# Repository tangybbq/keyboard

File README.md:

# David Brown (d3zd3z) keyboard designs

This repo captures the design files associated with my custom
keyboards.

These keyboards are primarily focused on Steno input, mainly using
[Plover](https://www.openstenoproject.org/plover/). In the spirit of
open steno, I have made these designs open. Anyone is free to make
designs based on these keyboards, for non-commercial purposes.  I am
releasing the designs under the [CC BY-NC
3.0](https://creativecommons.org/licenses/by-nc/3.0/) license.
Specifically, this means if you wish to sell a product based on the
design, you should talk to me.

## The "Jolt" keyboard

At this point, I've decided to give the keyboard a real name, hence "jolt".  The jolt 1 is still in
Eagle, and I may migrate the files here.

But, I have added the "jolt2".  The jolt2 is an experiment beyond just a traditional corne-like
keyboard, and something fully in 3-space, like the dactyl.  There are individual base plates for
left and right, and then small strips of 3 keys for each column.  The base PCB has 4 pairs of pin
headers to support these individual 3-key columns.  This will allow me to experiment with elevation
as well as just the X and Y position of each key.  I still want each column to be at the same
elevation, because I rely heavily on pressing keys together (both for my qwerty layout, and for
steno).

At this point, there are 4 PCBs here:

- [jolt2-left](jolt2/jolt2-left/): The layout of the left
  side using a directly assembled rp2040
- [jolt2-tiny2040-left](jolt2/jolt2-tiny2040-left/): The same left side pcb, but built around the [Pimoroni
  Tiny 2040](https://shop.pimoroni.com/products/tiny-2040?variant=39560012234835).  Note that only
  the left side needs the 8MB version (to hold the steno dictionary), but I just ordered all the
  same, and use the 8MB version on each side.
- [jolt2-tiny2040-right](jolt2/jolt2-tiny2040-right/): The Tiny 2040-based, made for the right side.
- [jolt2-verts](jolt2/jolt2-verts/): These are the small 3-key support boards.  It will take 28 of these,
  plus a left and a right to build a full keyboard.

In addition, there is also a [jolt2-pim-left](jolt2/jolt2-pim-left/), based around the [Pimoroni
PGA2350](https://shop.pimoroni.com/products/pga2350?variant=42092629229651).  There are numerous
errors in this that need to be fixed, as I messed up the reference numbers for the headers to the
key-boards.

## The "bletest2"

This isn't really a keyboard, but my experiments putting an nRF5340 module on a board.  This is work
in progress, and has numerous things I've discovered wrong with it.  I will work to improve it over
time:

- The power supply was suppose to auto switch between USB power and battery power.  However, I
  accidentally chose a boost converter instead of a boost/buck converter, and if USB is connected,
  all it does is fry everything on the board.  You can either leave out D1, or install a chain of
  diodes in its place (I used 5) to drop the voltage enough to make VBUS less than the 3.3.
  Auto-switching will probably end up preferring the battery, though, so I just recommend removing
  D1 entirely, and powering the board off of the batteries.
- The RGB LEDs don't work.  I'm not quite sure what is wrong, as I see no signal on the DIN pin.  I
  maybe have issues, given the difficult of properly soldering down the BLE module.
- The LEDs probably need a 5V supply, which isn't readily available.  Realistically, if I build a
  battery power device, I'll likely just use an analog RGB component, and use 3 gpios with PWM.

The intent was to be able to remove the various jumpers, and use the Power Profiler Kit II to
observer power consumption.  Despite rev 2, I'm still not far enough along with this to be able to
do that meaningfully.

## The "shield-kb1"

This is an Arduino-style shield, designed to plug into the nRF5340 DK.  It provides non-working
LEDs, a 2x2 keyboard matrix, and inter-board headers for left and right that should allow it to talk
to the jolt or proto3 designs.

## The "proto3"

This is basically the same design as the proto2, but with a third row.
The qmk supports an easier qwerty mode, but still with a modified
homerow modifier support (I use the lower row as it has slightly fewer
rollover conflicts).

The BOM is the same as the proto2, but it will need 42 diodes.

## The "proto2"

For lack of a better name, this first design is called the "proto2".

There was an earlier prototype, that was handwired, and rather
fragile.  This is the first version I would consider to be a usable
keyboard.  In the above pictures, the left half has the MCU (Pro Micro
RP2040) soldered directly to a header, soldered to the PCB, and the
right one uses a socket.

To build this, in addition to the PCBs, you will need

- 2 [Pro Micro RP2040](https://www.sparkfun.com/products/18288)
  boards.  At the time of my build, these are running about $11, and
  seem readily available.
- 30 Kailh Choc switches.  I sourced mine from
  [Mkultra](https://mkultra.click/choc-switches).  I recommend the
  "pink" version, which has 20gf springs, and I find work well.
- 30 keycaps for these switches.  I used the [MBK Factory
  Colors](https://mkultra.click/mbk-factory-colors/) keycaps, which
  allows me to make the "primary" keys stand out a little, and just
  looks rather nice.
- 30 general purpose SOD123 diodes.  I got
  [BAV19W](https://www.digikey.com/en/products/detail/smc-diode-solutions/BAV19W/5993796),
  although almost any diode will work for this.
- 2 or 4 5-pin right angle headers.  Two are needed for the
  communication between the boards.  The others are interested if you
  want to use SWD, since the RP2040 Pro Micro inconveniently puts
  these connectors on the underside of the board.

The PCB is reversable.  The RP2040 board should be mounted in the
labeled holes, which is always the left set when viewed from the top.
The diodes are intended to be soldered to the bottom side of the
board.

I have also a case design that can be 3d printed.  The models are for
the right side. Use your slicing software to mirror about the X axis
to print the pieces for the other side.

The firmware I am using for this keyboard is in my fork of
[QMK](https://github.com/tangybbq/qmk_firmware/tree/proto2).

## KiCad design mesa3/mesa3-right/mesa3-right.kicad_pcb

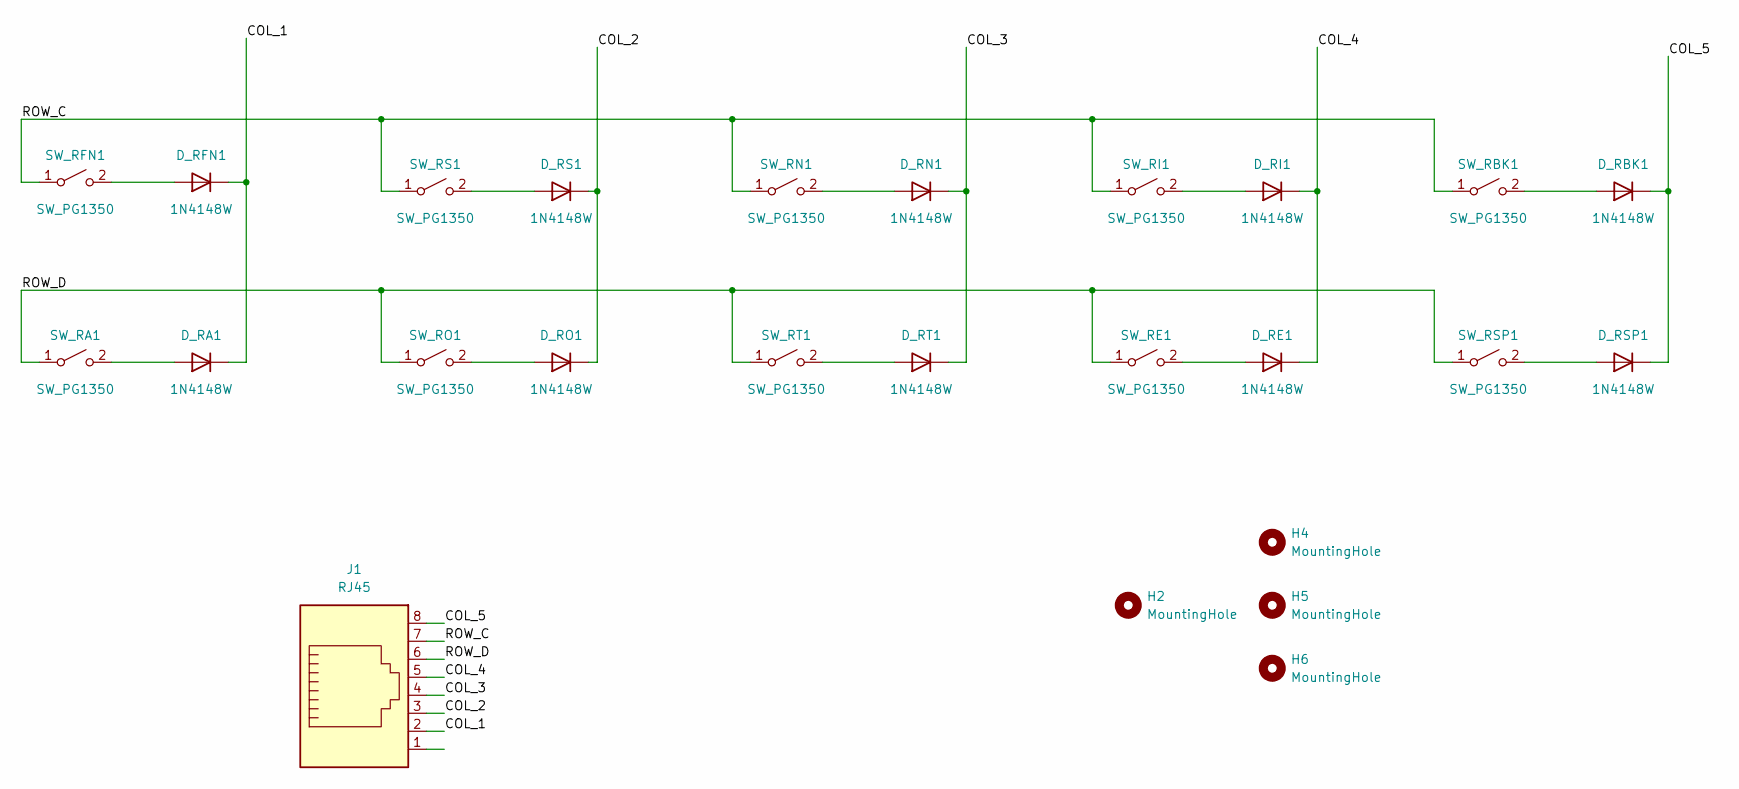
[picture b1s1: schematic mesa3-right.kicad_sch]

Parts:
D_RA1: 1N4148W; D_SOD-123
D_RBK1: 1N4148W; D_SOD-123
D_RE1: 1N4148W; D_SOD-123
D_RFN1: 1N4148W; D_SOD-123
D_RI1: 1N4148W; D_SOD-123
D_RN1: 1N4148W; D_SOD-123
D_RO1: 1N4148W; D_SOD-123
D_RS1: 1N4148W; D_SOD-123
D_RSP1: 1N4148W; D_SOD-123
D_RT1: 1N4148W; D_SOD-123
H2, H4, H5, H6: MountingHole; MountingHole_2.2mm_M2
J1: RJ45; RJ45_Amphenol_54602-x08_Horizontal
SW_RA1: SW_PG1350; Kailh_socket_PG1350
SW_RBK1: SW_PG1350; Kailh_socket_PG1350
SW_RE1: SW_PG1350; Kailh_socket_PG1350
SW_RFN1: SW_PG1350; Kailh_socket_PG1350
SW_RI1: SW_PG1350; Kailh_socket_PG1350
SW_RN1: SW_PG1350; Kailh_socket_PG1350
SW_RO1: SW_PG1350; Kailh_socket_PG1350
SW_RS1: SW_PG1350; Kailh_socket_PG1350
SW_RSP1: SW_PG1350; Kailh_socket_PG1350
SW_RT1: SW_PG1350; Kailh_socket_PG1350

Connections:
/COL_1: D_RA1.1 (K), D_RFN1.1 (K), J1.2
/COL_2: D_RO1.1 (K), D_RS1.1 (K), J1.3
/COL_3: D_RN1.1 (K), D_RT1.1 (K), J1.4
/COL_4: D_RE1.1 (K), D_RI1.1 (K), J1.5
/COL_5: D_RBK1.1 (K), D_RSP1.1 (K), J1.8
/ROW_C: J1.7, SW_RBK1.1 (A), SW_RFN1.1 (A), SW_RI1.1 (A), SW_RN1.1 (A), SW_RS1.1 (A)
/ROW_D: J1.6, SW_RA1.1 (A), SW_RE1.1 (A), SW_RO1.1 (A), SW_RSP1.1 (A), SW_RT1.1 (A)
unnamed: D_RA1.2 (A), SW_RA1.2 (B)
unnamed: D_RBK1.2 (A), SW_RBK1.2 (B)
unnamed: D_RE1.2 (A), SW_RE1.2 (B)
unnamed: D_RFN1.2 (A), SW_RFN1.2 (B)
unnamed: D_RI1.2 (A), SW_RI1.2 (B)
unnamed: D_RN1.2 (A), SW_RN1.2 (B)
unnamed: D_RO1.2 (A), SW_RO1.2 (B)
unnamed: D_RS1.2 (A), SW_RS1.2 (B)
unnamed: D_RSP1.2 (A), SW_RSP1.2 (B)
unnamed: D_RT1.2 (A), SW_RT1.2 (B)

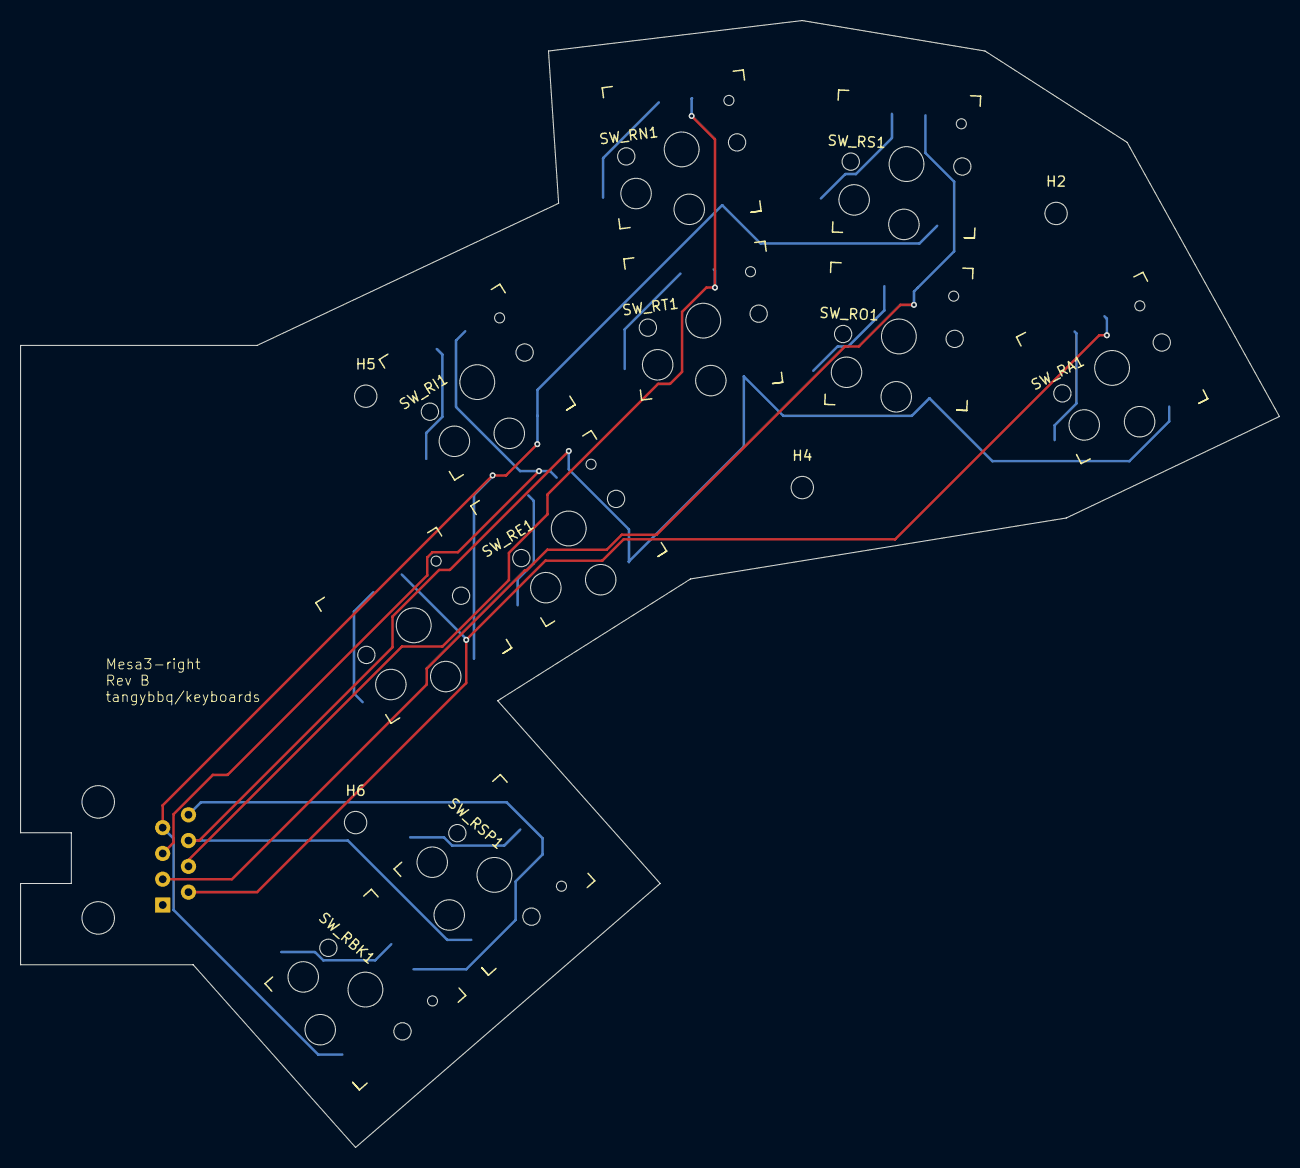
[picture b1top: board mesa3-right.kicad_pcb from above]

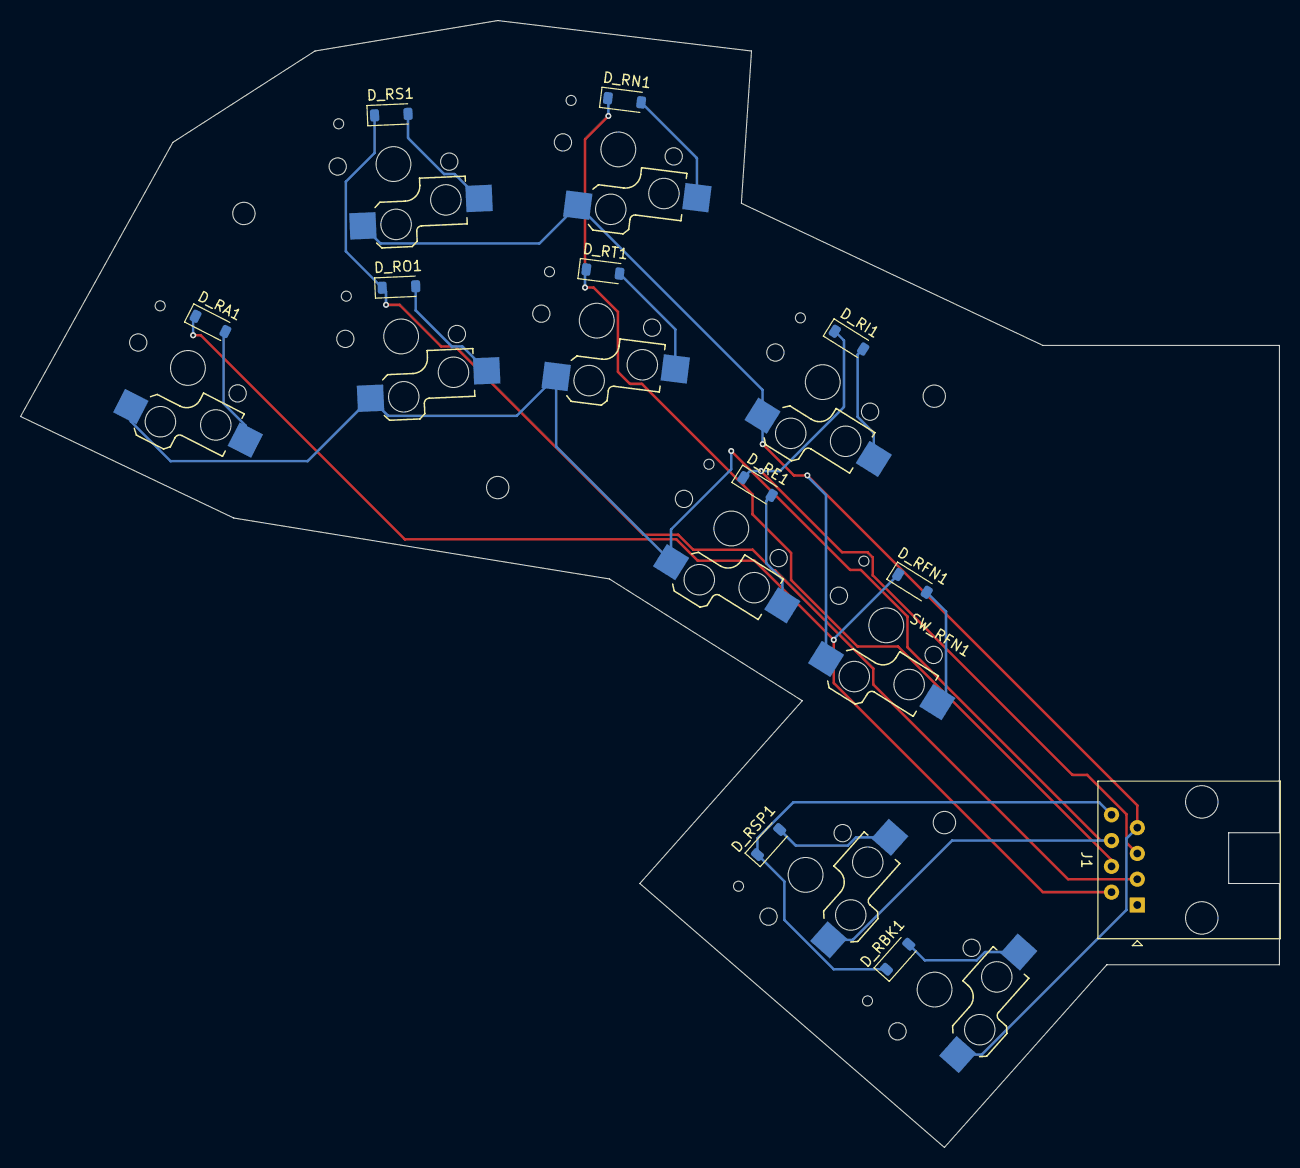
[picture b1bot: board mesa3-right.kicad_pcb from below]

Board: 2 copper layers, 124.0 x 111.0 mm, 25 parts (11 on the bottom side), 17 nets.

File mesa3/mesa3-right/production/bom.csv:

Designator,Footprint,Quantity,Value,LCSC Part #
"D_RA1, D_RBK1, D_RE1, D_RI1, D_RN1, D_RO1, D_RS1, D_RSP1, D_RT1",D_SOD-123,9,1N4148W,
J1,RJ45_Amphenol_54602-x08_Horizontal,1,RJ45,
"SW_RA1, SW_RBK1, SW_RE1, SW_RI1, SW_RN1, SW_RO1, SW_RS1, SW_RSP1, SW_RT1",Kailh_socket_PG1350,9,SW_PG1350,

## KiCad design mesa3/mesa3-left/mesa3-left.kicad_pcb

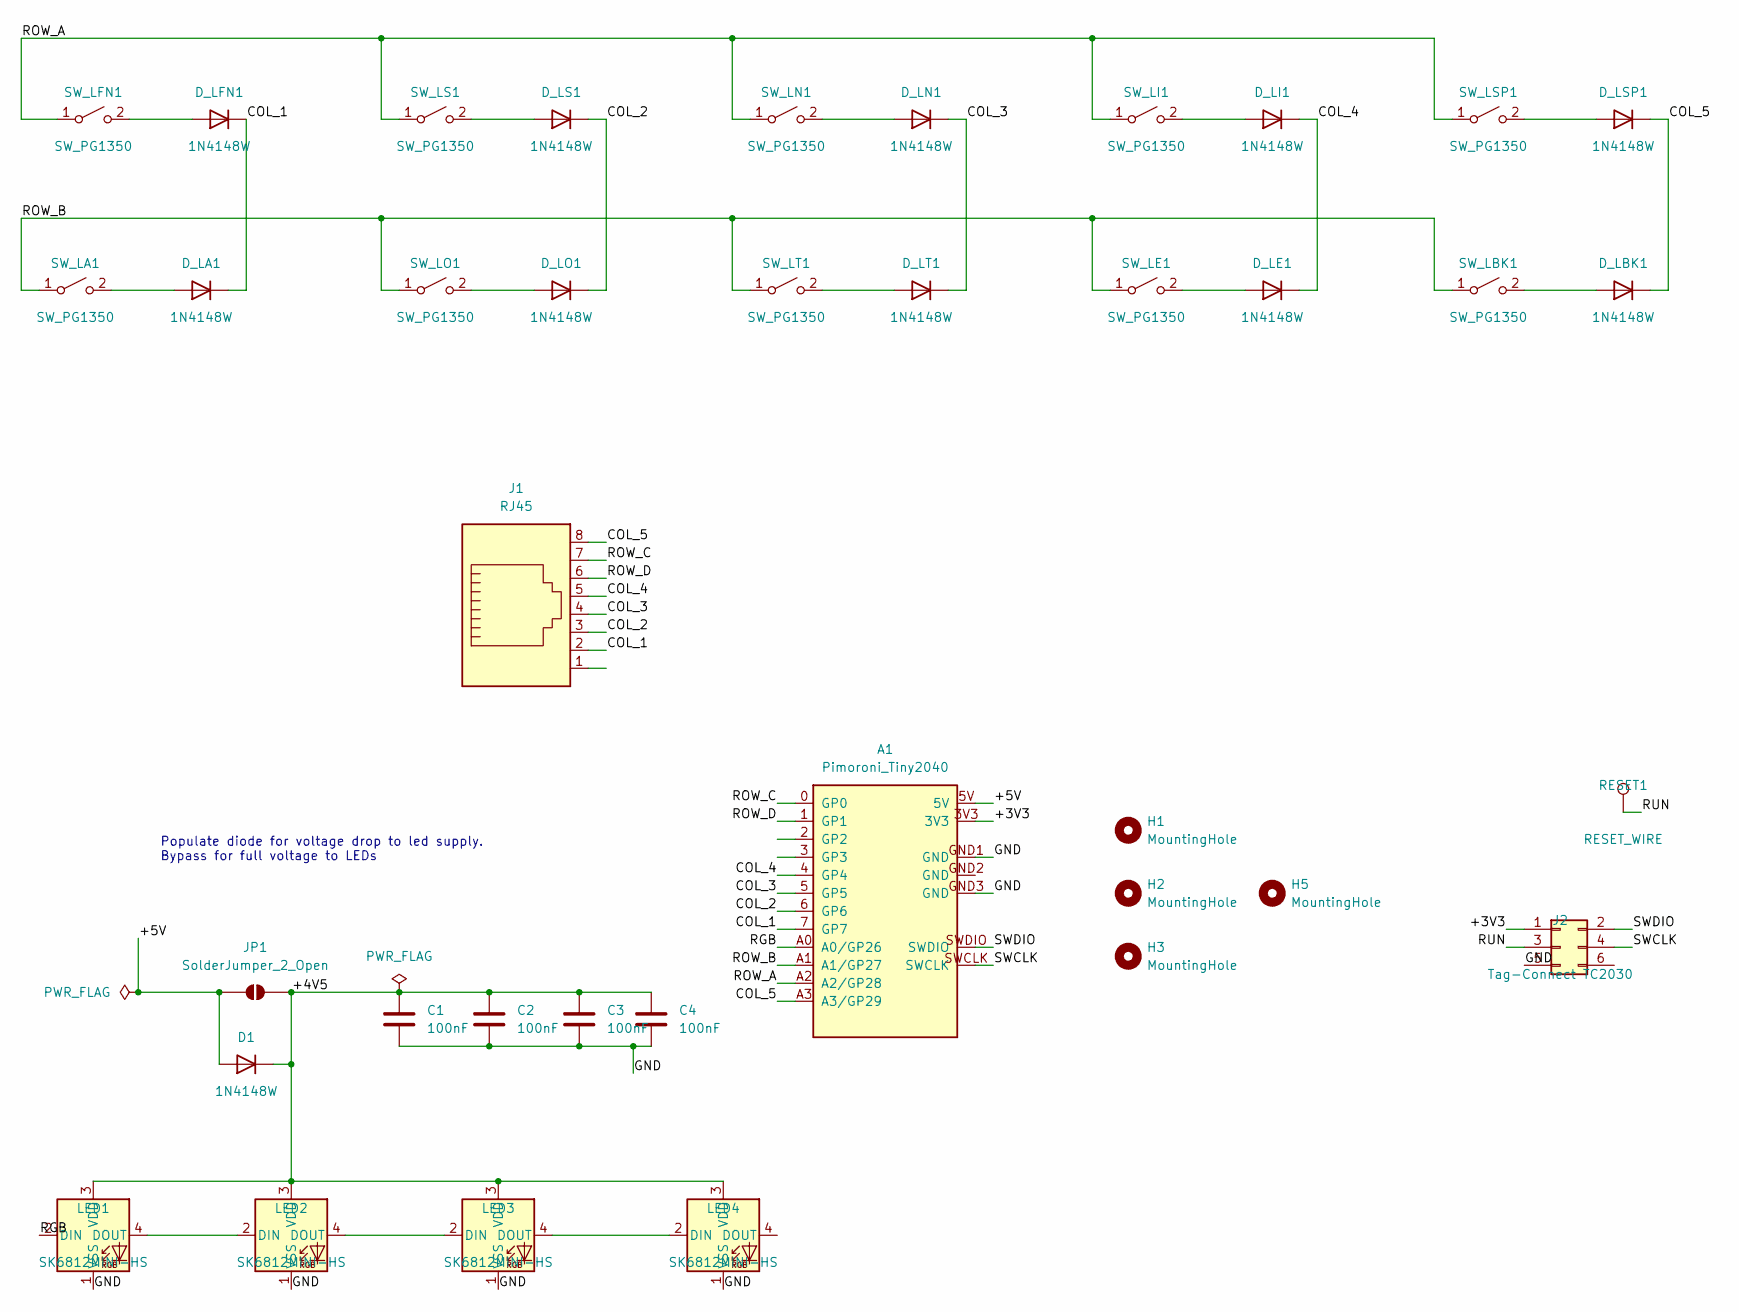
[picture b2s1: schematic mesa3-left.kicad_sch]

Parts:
A1: Pimoroni_Tiny2040
C1, C2, C3, C4: 100nF; C_0603_1608Metric_Pad1.08x0.95mm_HandSolder
D1: 1N4148W; D_SOD-123
D_LA1: 1N4148W; D_SOD-123
D_LBK1: 1N4148W; D_SOD-123
D_LE1: 1N4148W; D_SOD-123
D_LFN1: 1N4148W; D_SOD-123
D_LI1: 1N4148W; D_SOD-123
D_LN1: 1N4148W; D_SOD-123
D_LO1: 1N4148W; D_SOD-123
D_LS1: 1N4148W; D_SOD-123
D_LSP1: 1N4148W; D_SOD-123
D_LT1: 1N4148W; D_SOD-123
H1, H2, H3, H5: MountingHole; MountingHole_2.2mm_M2
J1: RJ45; RJ45_Amphenol_54602-x08_Horizontal
J2: Tag-Connect TC2030; Tag-Connect_TC2030-IDC-FP_2x03_P1.27mm_Vertical
JP1: SolderJumper_2_Open; SolderJumper-2_P1.3mm_Open_RoundedPad1.0x1.5mm
LED1, LED2, LED3, LED4: SK6812MINI-HS; SK6812-MINI-HS
RESET1: RESET_WIRE; TestPoint_Pad_2.0x2.0mm
SW_LA1: SW_PG1350; Kailh_socket_PG1350
SW_LBK1: SW_PG1350; Kailh_socket_PG1350
SW_LE1: SW_PG1350; Kailh_socket_PG1350
SW_LFN1: SW_PG1350; Kailh_socket_PG1350
SW_LI1: SW_PG1350; Kailh_socket_PG1350
SW_LN1: SW_PG1350; Kailh_socket_PG1350
SW_LO1: SW_PG1350; Kailh_socket_PG1350
SW_LS1: SW_PG1350; Kailh_socket_PG1350
SW_LSP1: SW_PG1350; Kailh_socket_PG1350
SW_LT1: SW_PG1350; Kailh_socket_PG1350

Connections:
/+3V3: A1.3V3, J2.1
/+4V5: C1.1, C2.1, C3.1, C4.1, D1.1 (K), JP1.2 (B), LED1.3 (VDD), LED2.3 (VDD), LED3.3 (VDD), LED4.3 (VDD)
/+5V: A1.5V, D1.2 (A), JP1.1 (A)
/COL_1: A1.7 (GP7), D_LA1.1 (K), D_LFN1.1 (K), J1.2
/COL_2: A1.6 (GP6), D_LO1.1 (K), D_LS1.1 (K), J1.3
/COL_3: A1.5 (GP5), D_LN1.1 (K), D_LT1.1 (K), J1.4
/COL_4: A1.4 (GP4), D_LE1.1 (K), D_LI1.1 (K), J1.5
/COL_5: A1.A3 (A3/GP29), D_LBK1.1 (K), D_LSP1.1 (K), J1.8
/GND: A1.GND1 (GND), A1.GND3 (GND), C1.2, C2.2, C3.2, C4.2, J2.5, LED1.1 (VSS), LED2.1 (VSS), LED3.1 (VSS), LED4.1 (VSS)
/RGB: A1.A0 (A0/GP26), LED1.2 (DIN)
/ROW_A: A1.A2 (A2/GP28), SW_LFN1.1 (A), SW_LI1.1 (A), SW_LN1.1 (A), SW_LS1.1 (A), SW_LSP1.1 (A)
/ROW_B: A1.A1 (A1/GP27), SW_LA1.1 (A), SW_LBK1.1 (A), SW_LE1.1 (A), SW_LO1.1 (A), SW_LT1.1 (A)
/ROW_C: A1.0 (GP0), J1.7
/ROW_D: A1.1 (GP1), J1.6
/RUN: J2.3, RESET1.1 (1_1)
/SWCLK: A1.SWCLK, J2.4
/SWDIO: A1.SWDIO, J2.2
unnamed: D_LA1.2 (A), SW_LA1.2 (B)
unnamed: D_LBK1.2 (A), SW_LBK1.2 (B)
unnamed: D_LE1.2 (A), SW_LE1.2 (B)
unnamed: D_LFN1.2 (A), SW_LFN1.2 (B)
unnamed: D_LI1.2 (A), SW_LI1.2 (B)
unnamed: D_LN1.2 (A), SW_LN1.2 (B)
unnamed: D_LO1.2 (A), SW_LO1.2 (B)
unnamed: D_LS1.2 (A), SW_LS1.2 (B)
unnamed: D_LSP1.2 (A), SW_LSP1.2 (B)
unnamed: D_LT1.2 (A), SW_LT1.2 (B)
unnamed: LED1.4 (DOUT), LED2.2 (DIN)
unnamed: LED2.4 (DOUT), LED3.2 (DIN)
unnamed: LED3.4 (DOUT), LED4.2 (DIN)

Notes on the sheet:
Populate diode for voltage drop to led supply. Bypass for full voltage to LEDs

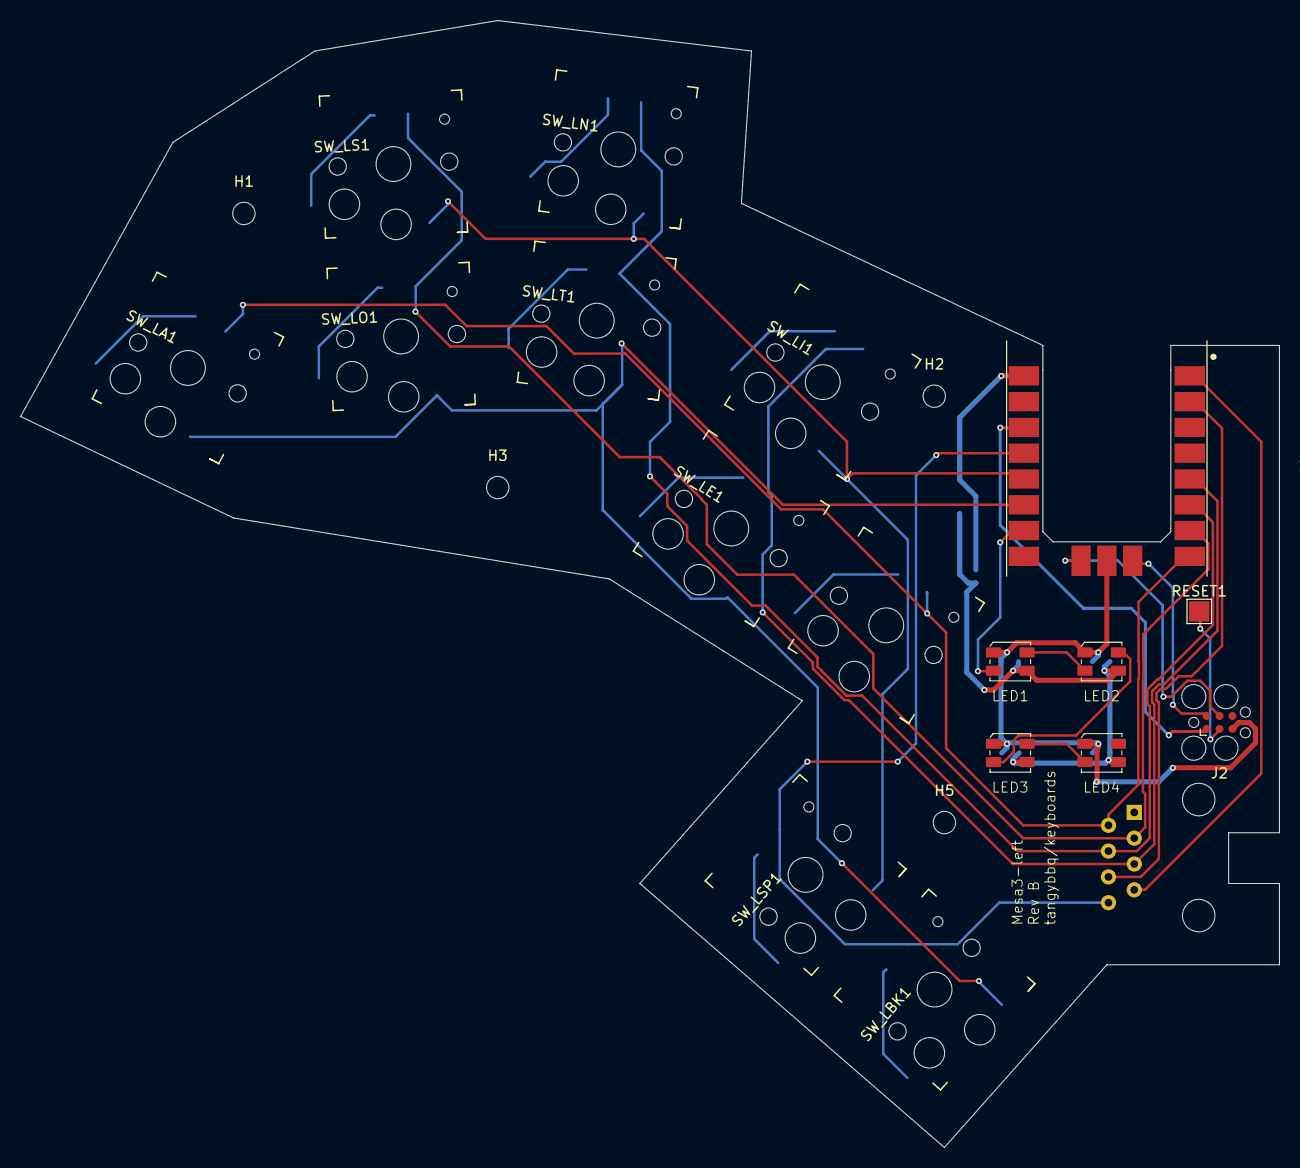
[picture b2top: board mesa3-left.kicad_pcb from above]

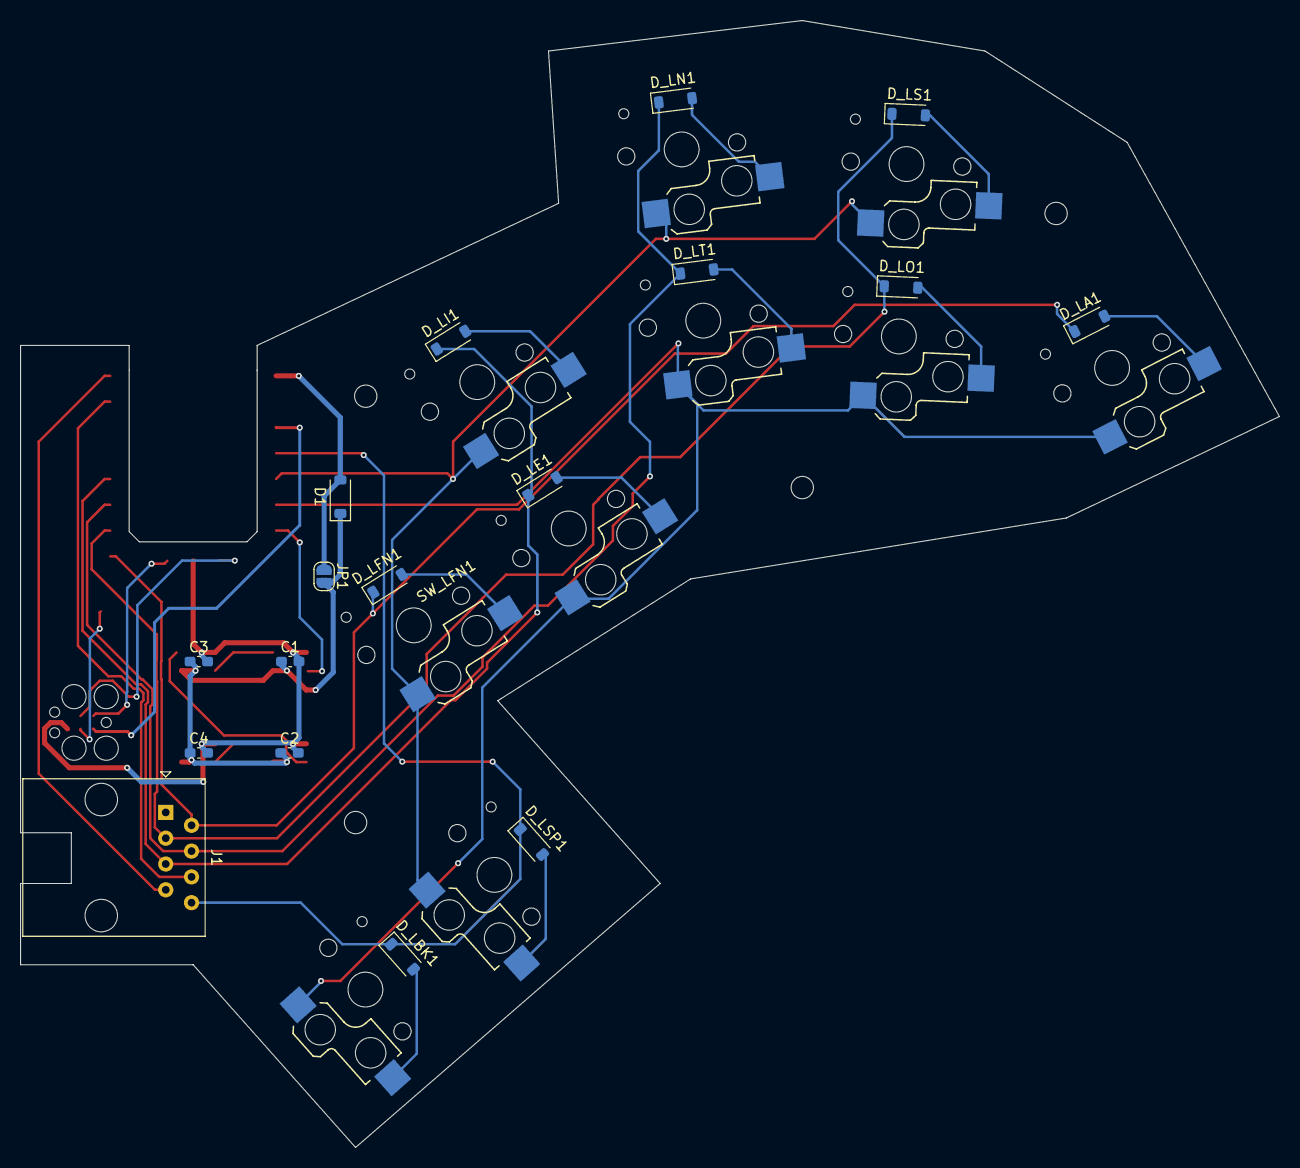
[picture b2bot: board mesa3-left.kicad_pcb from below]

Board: 2 copper layers, 124.0 x 111.0 mm, 38 parts (17 on the bottom side), 30 nets.

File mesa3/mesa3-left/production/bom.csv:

Designator,Footprint,Quantity,Value,LCSC Part #
A1,Pimoroni_Tiny2040,1,Pimoroni_Tiny2040,
"C1, C2, C3, C4",0603,4,100nF,
"D1, D_LA1, D_LBK1, D_LE1, D_LI1, D_LN1, D_LO1, D_LS1, D_LSP1, D_LT1",D_SOD-123,10,1N4148W,
J1,RJ45_Amphenol_54602-x08_Horizontal,1,RJ45,
J2,Tag-Connect_TC2030-IDC-FP_2x03_P1.27mm_Vertical,1,Tag-Connect TC2030,
"LED1, LED2, LED3, LED4",SK6812-MINI-HS,4,SK6812MINI-HS,
RESET1,TestPoint_Pad_2.0x2.0mm,1,RESET_WIRE,
"SW_LA1, SW_LBK1, SW_LE1, SW_LI1, SW_LN1, SW_LO1, SW_LS1, SW_LSP1, SW_LT1",Kailh_socket_PG1350,9,SW_PG1350,

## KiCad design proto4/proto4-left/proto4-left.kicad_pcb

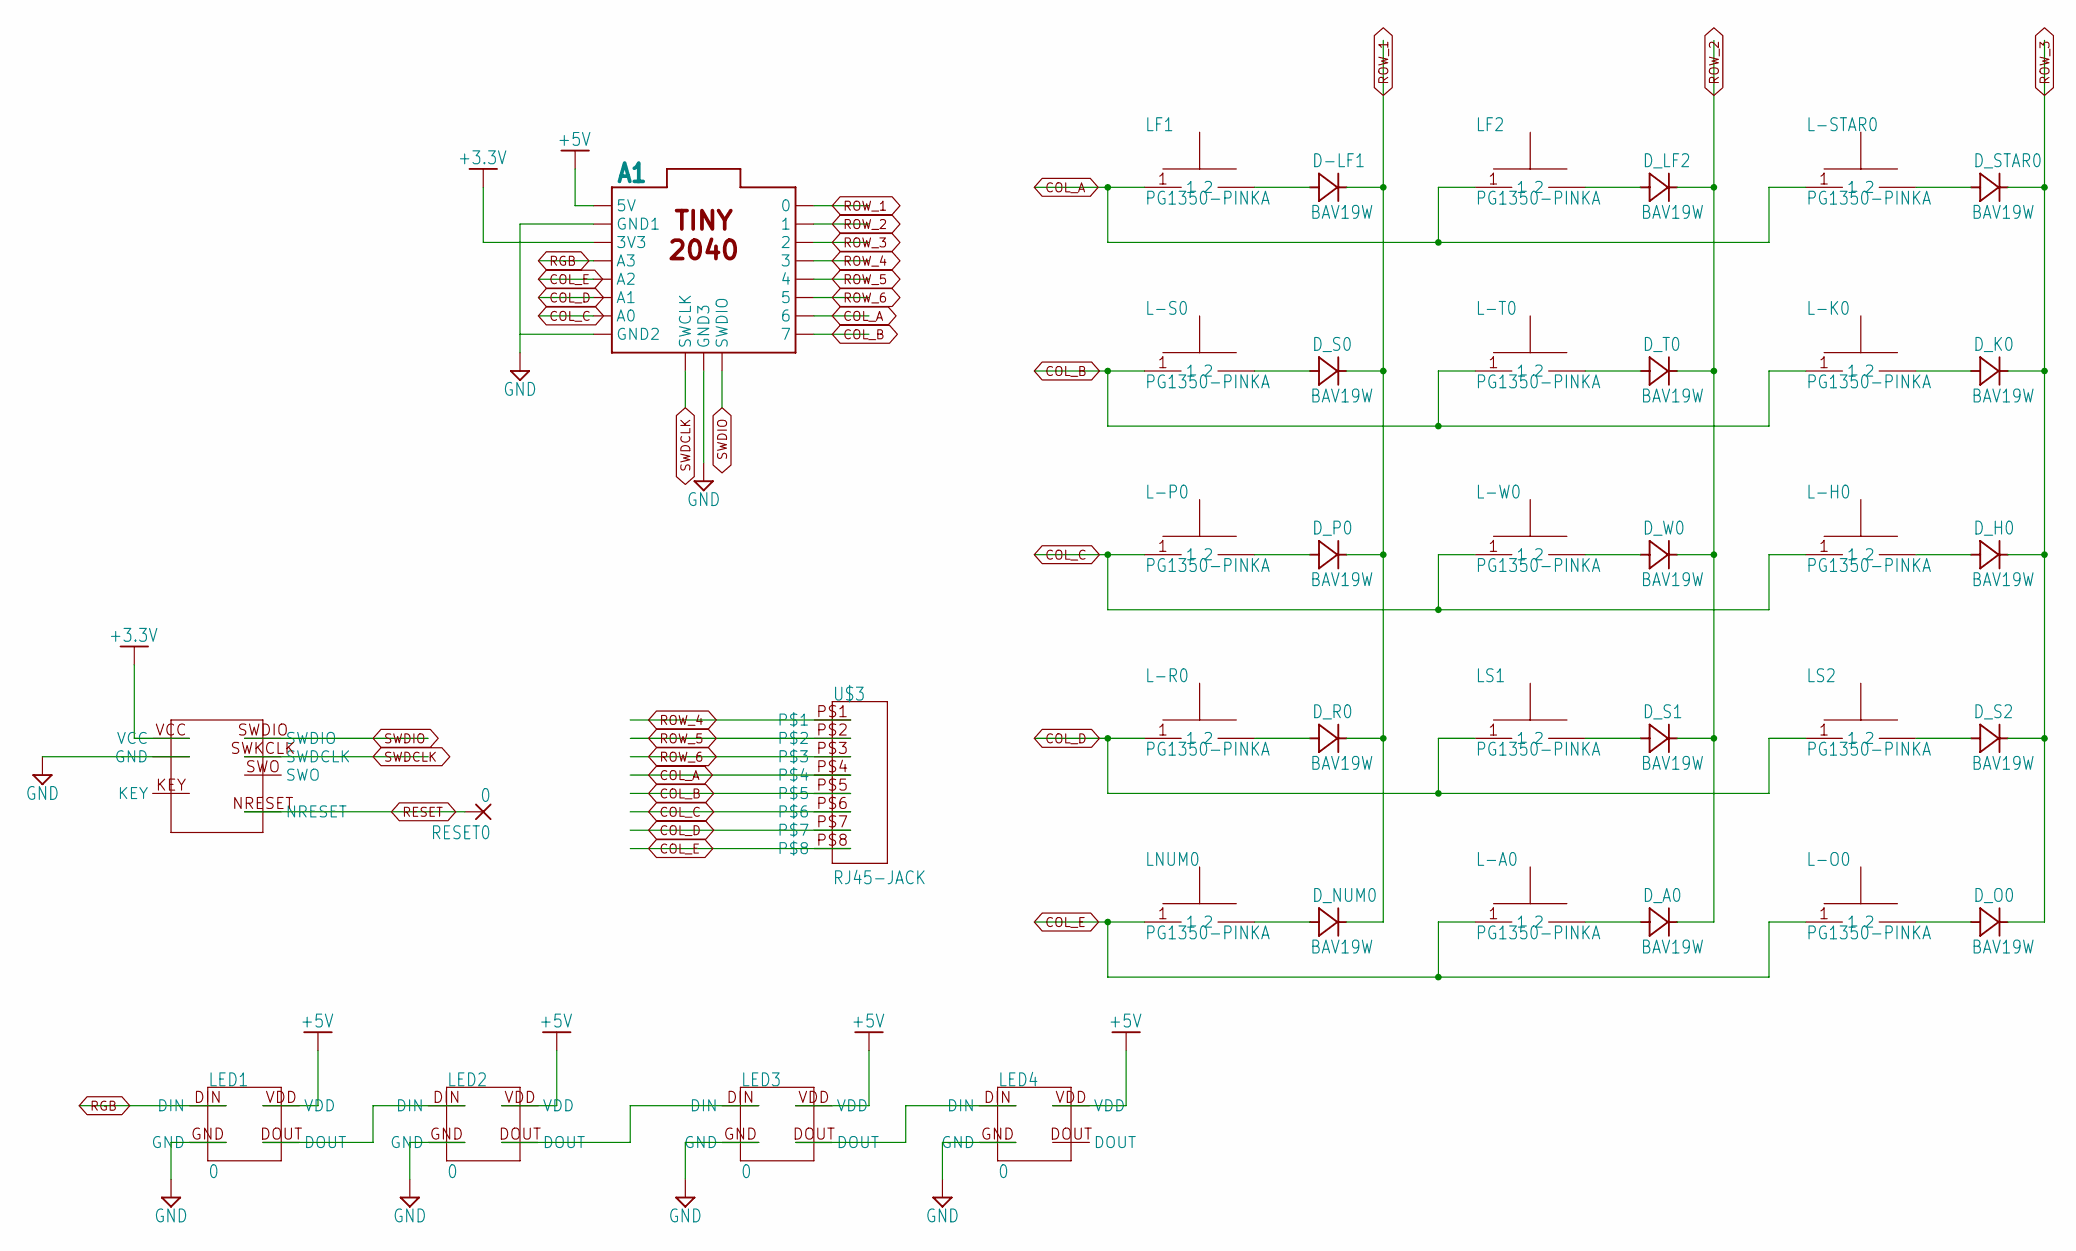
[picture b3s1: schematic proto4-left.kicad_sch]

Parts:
A1: TINY2040
D-LF1: BAV19W; SOD123
D_A0: BAV19W; SOD123
D_H0: BAV19W; SOD123
D_K0: BAV19W; SOD123
D_LF2: BAV19W; SOD123
D_NUM0: BAV19W; SOD123
D_O0: BAV19W; SOD123
D_P0: BAV19W; SOD123
D_R0: BAV19W; SOD123
D_S0, D_S1, D_S2: BAV19W; SOD123
D_STAR0: BAV19W; SOD123
D_T0: BAV19W; SOD123
D_W0: BAV19W; SOD123
L-A0: PG1350-PINKA; PG1350
L-H0: PG1350-PINKA; PG1350
L-K0: PG1350-PINKA; PG1350
L-O0: PG1350-PINKA; PG1350
L-P0: PG1350-PINKA; PG1350
L-R0: PG1350-PINKA; PG1350
L-S0: PG1350-PINKA; PG1350
L-STAR0: PG1350-PINKA; PG1350
L-T0: PG1350-PINKA; PG1350
L-W0: PG1350-PINKA; PG1350
LED1, LED2, LED3, LED4: 0; SK6812-MINI-HS
LF1, LF2: PG1350-PINKA; PG1350
LNUM0: PG1350-PINKA; PG1350
LS1, LS2: PG1350-PINKA; PG1350
RESET0: 0; SMD1,27-2,54
U$2: CORTEX-M0; CORTEX-M10
U$3: RJ45-JACK; C-BMJ-0051-RJ45

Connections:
+3.3V: A1.3V3, U$2.VCC
+5V: A1.5V, LED1.VDD, LED2.VDD, LED3.VDD, LED4.VDD
COL_A: A1.6, L-STAR0.1, LF1.1, LF2.1, U$3.P$4
COL_B: A1.7, L-K0.1, L-S0.1, L-T0.1, U$3.P$5
COL_C: A1.A0, L-H0.1, L-P0.1, L-W0.1, U$3.P$6
COL_D: A1.A1, L-R0.1, LS1.1, LS2.1, U$3.P$7
COL_E: A1.A2, L-A0.1, L-O0.1, LNUM0.1, U$3.P$8
GND: A1.GND1, A1.GND3, LED1.GND, LED2.GND, LED3.GND, LED4.GND, U$2.GND2 (GND), U$2.GND3 (GND), U$2.GNDDETECT (GND)
unnamed: D-LF1.A, LF1.2B (2), LF1.2T (2)
unnamed: D_LF2.A, LF2.2B (2), LF2.2T (2)
unnamed: D_STAR0.A, L-STAR0.2B (2), L-STAR0.2T (2)
unnamed: D_S0.A, L-S0.2B (2), L-S0.2T (2)
unnamed: D_T0.A, L-T0.2B (2), L-T0.2T (2)
unnamed: D_K0.A, L-K0.2B (2), L-K0.2T (2)
unnamed: D_P0.A, L-P0.2B (2), L-P0.2T (2)
unnamed: D_W0.A, L-W0.2B (2), L-W0.2T (2)
unnamed: D_H0.A, L-H0.2B (2), L-H0.2T (2)
unnamed: D_R0.A, L-R0.2B (2), L-R0.2T (2)
unnamed: D_S1.A, LS1.2B (2), LS1.2T (2)
unnamed: D_S2.A, LS2.2B (2), LS2.2T (2)
unnamed: D_NUM0.A, LNUM0.2B (2), LNUM0.2T (2)
unnamed: D_A0.A, L-A0.2B (2), L-A0.2T (2)
unnamed: D_O0.A, L-O0.2B (2), L-O0.2T (2)
unnamed: LED3.DOUT, LED4.DIN
unnamed: LED2.DOUT, LED3.DIN
unnamed: LED1.DOUT, LED2.DIN
RESET: RESET0.1, U$2.NRESET
RGB: A1.A3, LED1.DIN
ROW_1: A1.0, D-LF1.C, D_NUM0.C, D_P0.C, D_R0.C, D_S0.C
ROW_2: A1.1, D_A0.C, D_LF2.C, D_S1.C, D_T0.C, D_W0.C
ROW_3: A1.2, D_H0.C, D_K0.C, D_O0.C, D_S2.C, D_STAR0.C
ROW_4: A1.3, U$3.P$1
ROW_5: A1.4, U$3.P$2
ROW_6: A1.5, U$3.P$3
SWDCLK: A1.SWCLK, U$2.SWKCLK (SWDCLK)
SWDIO: A1.SWDIO, U$2.SWDIO

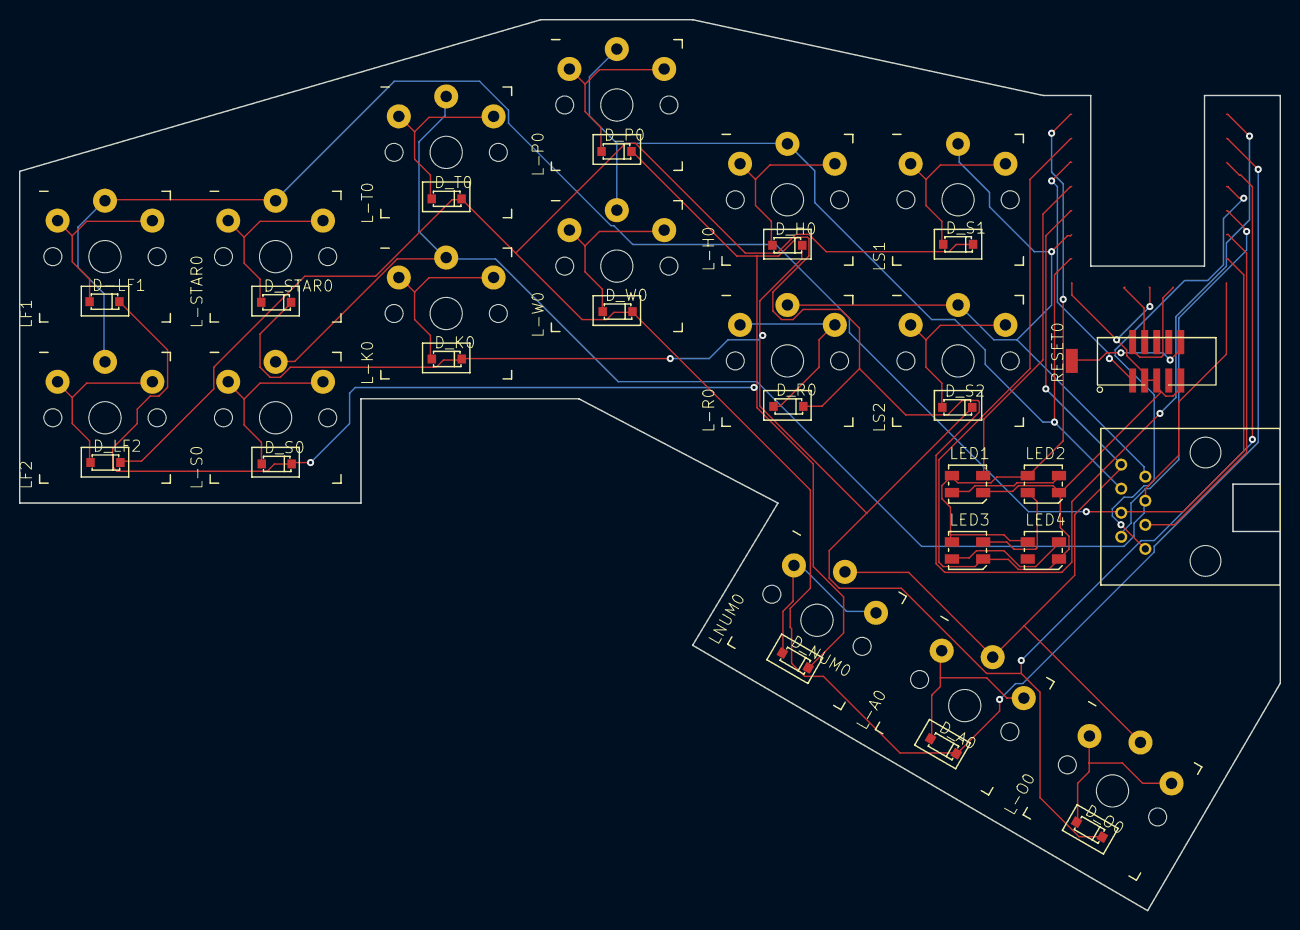
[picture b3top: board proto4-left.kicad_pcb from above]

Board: 2 copper layers, 133.0 x 94.0 mm, 37 parts (0 on the bottom side), 29 nets.

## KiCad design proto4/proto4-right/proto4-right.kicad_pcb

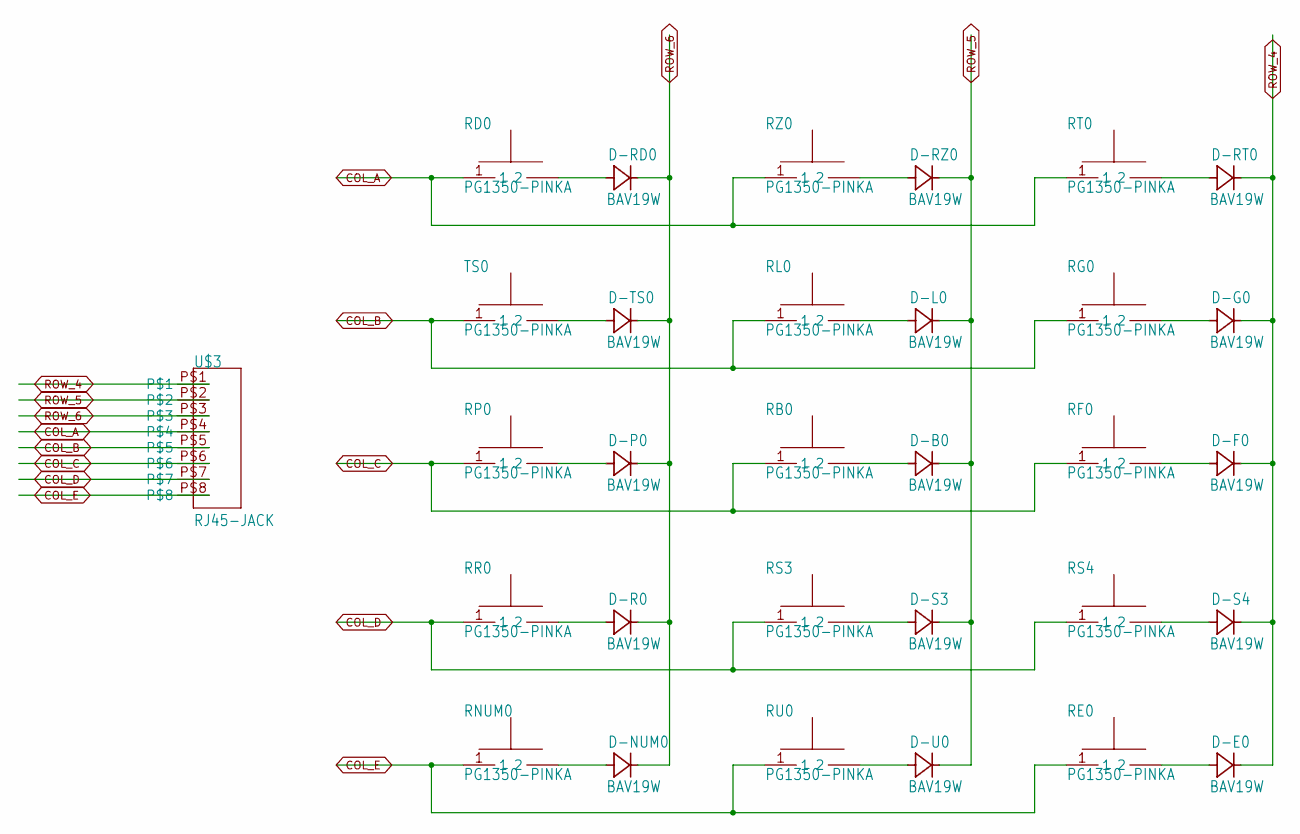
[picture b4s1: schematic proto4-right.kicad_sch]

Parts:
D-B0: BAV19W; SOD123
D-E0: BAV19W; SOD123
D-F0: BAV19W; SOD123
D-G0: BAV19W; SOD123
D-L0: BAV19W; SOD123
D-NUM0: BAV19W; SOD123
D-P0: BAV19W; SOD123
D-R0: BAV19W; SOD123
D-RD0: BAV19W; SOD123
D-RT0: BAV19W; SOD123
D-RZ0: BAV19W; SOD123
D-S3, D-S4: BAV19W; SOD123
D-TS0: BAV19W; SOD123
D-U0: BAV19W; SOD123
RB0: PG1350-PINKA; PG1350
RD0: PG1350-PINKA; PG1350
RE0: PG1350-PINKA; PG1350
RF0: PG1350-PINKA; PG1350
RG0: PG1350-PINKA; PG1350
RL0: PG1350-PINKA; PG1350
RNUM0: PG1350-PINKA; PG1350
RP0: PG1350-PINKA; PG1350
RR0: PG1350-PINKA; PG1350
RS3, RS4: PG1350-PINKA; PG1350
RT0: PG1350-PINKA; PG1350
RU0: PG1350-PINKA; PG1350
RZ0: PG1350-PINKA; PG1350
TS0: PG1350-PINKA; PG1350
U$3: RJ45-JACK; C-BMJ-0051-RJ45

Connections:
COL_A: RD0.1, RT0.1, RZ0.1, U$3.P$4
COL_B: RG0.1, RL0.1, TS0.1, U$3.P$5
COL_C: RB0.1, RF0.1, RP0.1, U$3.P$6
COL_D: RR0.1, RS3.1, RS4.1, U$3.P$7
COL_E: RE0.1, RNUM0.1, RU0.1, U$3.P$8
unnamed: D-RD0.A, RD0.2B (2), RD0.2T (2)
unnamed: D-RZ0.A, RZ0.2B (2), RZ0.2T (2)
unnamed: D-RT0.A, RT0.2B (2), RT0.2T (2)
unnamed: D-TS0.A, TS0.2B (2), TS0.2T (2)
unnamed: D-L0.A, RL0.2B (2), RL0.2T (2)
unnamed: D-G0.A, RG0.2B (2), RG0.2T (2)
unnamed: D-P0.A, RP0.2B (2), RP0.2T (2)
unnamed: D-B0.A, RB0.2B (2), RB0.2T (2)
unnamed: D-F0.A, RF0.2B (2), RF0.2T (2)
unnamed: D-R0.A, RR0.2B (2), RR0.2T (2)
unnamed: D-S3.A, RS3.2B (2), RS3.2T (2)
unnamed: D-S4.A, RS4.2B (2), RS4.2T (2)
unnamed: D-NUM0.A, RNUM0.2B (2), RNUM0.2T (2)
unnamed: D-U0.A, RU0.2B (2), RU0.2T (2)
unnamed: D-E0.A, RE0.2B (2), RE0.2T (2)
ROW_4: D-E0.C, D-F0.C, D-G0.C, D-RT0.C, D-S4.C, U$3.P$1
ROW_5: D-B0.C, D-L0.C, D-RZ0.C, D-S3.C, D-U0.C, U$3.P$2
ROW_6: D-NUM0.C, D-P0.C, D-R0.C, D-RD0.C, D-TS0.C, U$3.P$3
